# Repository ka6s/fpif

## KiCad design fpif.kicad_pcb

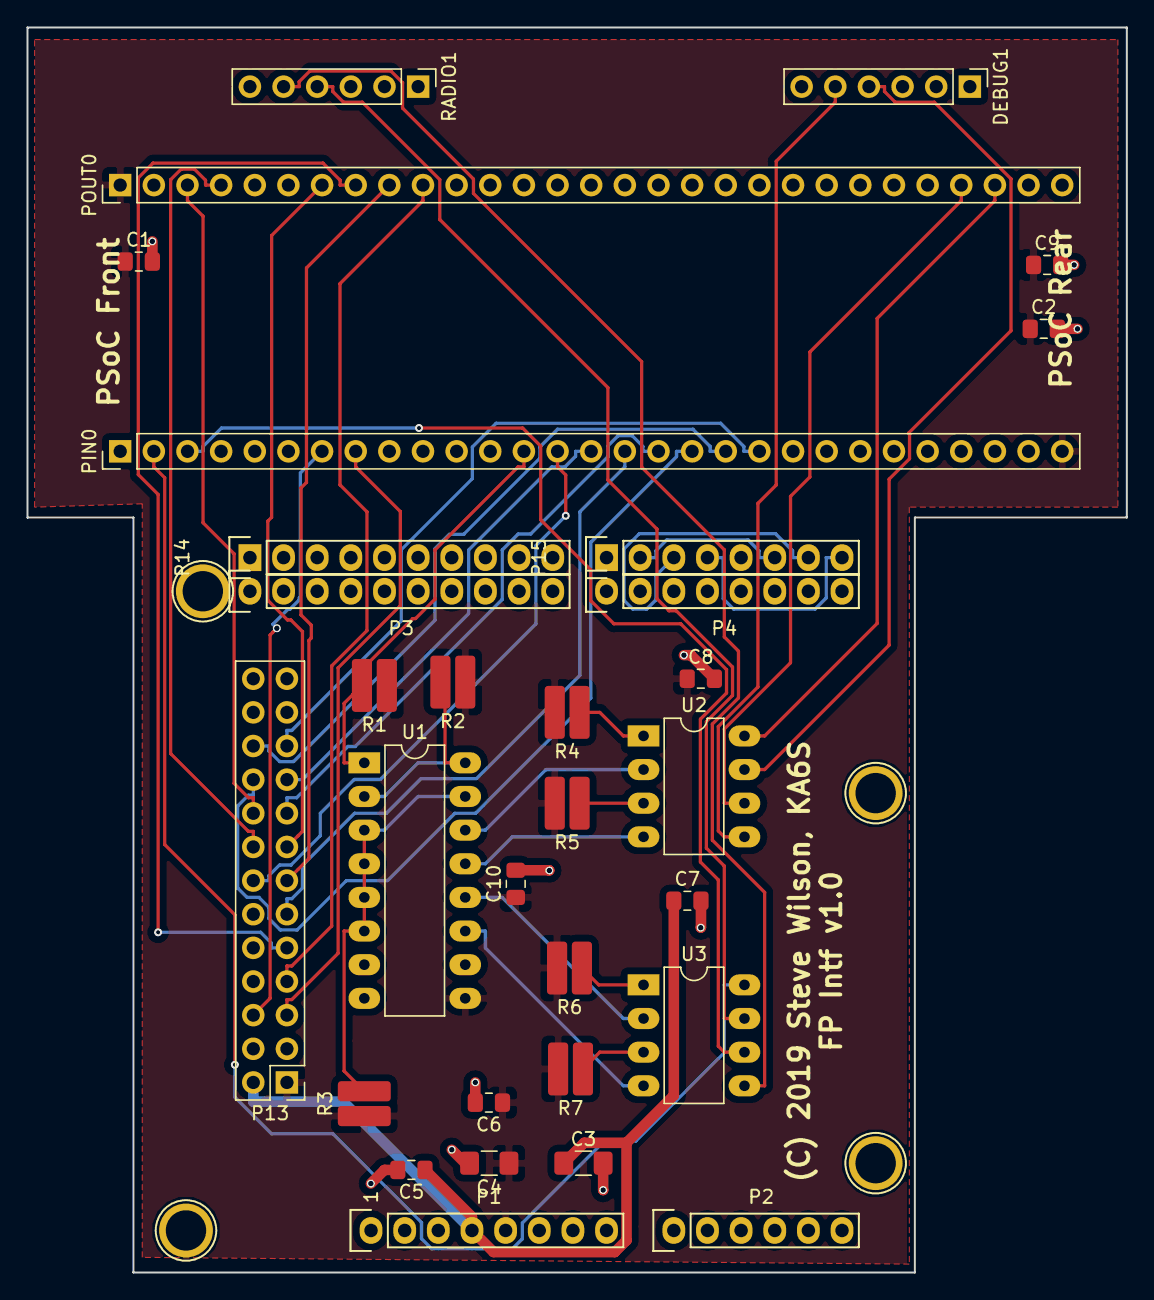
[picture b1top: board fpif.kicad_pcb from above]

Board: 2 copper layers, 83.0 x 94.0 mm, 35 parts (0 on the bottom side), 40 nets.

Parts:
C1, C7, C8, C9, C10: 0.01uF; C_0805_2012Metric_Pad1.15x1.40mm_HandSolder
C2, C5, C6: 1uF; C_0805_2012Metric_Pad1.15x1.40mm_HandSolder
C3, C4: 100uF; C_1206_3216Metric_Pad1.42x1.75mm_HandSolder
DEBUG1: CONN_01X06; PinHeader_1x06_P2.54mm_Vertical
P1: Power; Socket_Strip_Arduino_1x08
P2: Analog; Socket_Strip_Arduino_1x06
P3: Digital; Socket_Strip_Arduino_1x10
P4: Digital; Socket_Strip_Arduino_1x08
P5, P6, P7, P8: CONN_1; Arduino_1pin
P13: CONN_02X13; PinHeader_2x13_P2.54mm_Vertical
P14: Digital; Pin_Header_Straight_1x10
P15: Digital; Pin_Header_Straight_1x08
PIN0: CONN_01X29; PinHeader_1x29_P2.54mm_Vertical
POUT0: CONN_01X29; PinHeader_1x29_P2.54mm_Vertical
R1, R2, R3: 10K; R_0815_2038Metric_Pad1.53x4.00mm_HandSolder
R4, R5, R6, R7: 1K; R_0815_2038Metric_Pad1.53x4.00mm_HandSolder
RADIO1: CONN_01X06; PinHeader_1x06_P2.54mm_Vertical
U1: ULN2003; DIP-16_W7.62mm_LongPads
U2, U3: LAA110; DIP-8_W7.62mm_LongPads

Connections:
+3V3: C3.1, C5.1, C7.1, P1.4, P13.2
+5V: C1.1, C2.1, C4.1, C6.1, C8.1, C9.1, C10.1, P1.5, P13.1, PIN0.29, POUT0.1, R1.1, R2.1, R3.1, R4.2, R5.2, R6.2, R7.2, U1.9
/button_a_int: P13.22, PIN0.19
/button_b_int: P13.21, PIN0.20
/debug_rx: DEBUG1.4, U2.7
/debug_tx: DEBUG1.5, U2.5
/enca_clk: P13.7, POUT0.10
/enca_dat: P13.9, POUT0.8
/enca_sw: P13.11, PIN0.16
/encb_clk: P13.13, POUT0.9
/encb_dat: P13.15, POUT0.7
/encb_sw: P13.17, PIN0.17
/encc_clk: P13.18, POUT0.3
/encc_dat: P13.19, PIN0.15
/encc_sw: P13.20, PIN0.18
/i2c_scl: P13.6, PIN0.7
/i2c_sda: P13.5, PIN0.8
/pre_dbg_rx: POUT0.27, U2.8
/pre_dbg_tx: POUT0.26, U2.6
/pre_rdo_rx: PIN0.2, U3.8
/pre_rdo_tx: PIN0.3, U3.6
/radio_rx: RADIO1.4, U3.7
/radio_tx: RADIO1.5, U3.5
/relay_on_n: PIN0.13, R1.2, U1.1
/tune_cha: P13.14, PIN0.14
/tune_chb: P13.16, POUT0.4
/uart2_cts: P15.3, P15.7
/uart2_rts: P15.4, P15.8
/uart2_txd: P15.2, P15.6
GND: C1.2, C2.2, C3.2, C4.2, C5.2, C6.2, C7.2, C8.2, C9.2, C10.2, DEBUG1.1, P1.6, P1.7, P3.4, P13.23, P13.24, P14.2, PIN0.28, POUT0.2, POUT0.29, RADIO1.1, U1.8
unnamed: R2.2, U1.2, U1.16
unnamed: R3.2, U1.3, U1.4, U1.5, U1.6, U1.15
unnamed: R4.1, U2.1
unnamed: R5.1, U2.3
unnamed: R6.1, U3.1
unnamed: R7.1, U3.3
unnamed: U1.11, U3.4
unnamed: U1.12, U3.2
unnamed: U1.13, U2.4
unnamed: U1.14, U2.2

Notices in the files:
fpif.kicad_pcb:
(C) 2019 Steve Wilson, KA6S
